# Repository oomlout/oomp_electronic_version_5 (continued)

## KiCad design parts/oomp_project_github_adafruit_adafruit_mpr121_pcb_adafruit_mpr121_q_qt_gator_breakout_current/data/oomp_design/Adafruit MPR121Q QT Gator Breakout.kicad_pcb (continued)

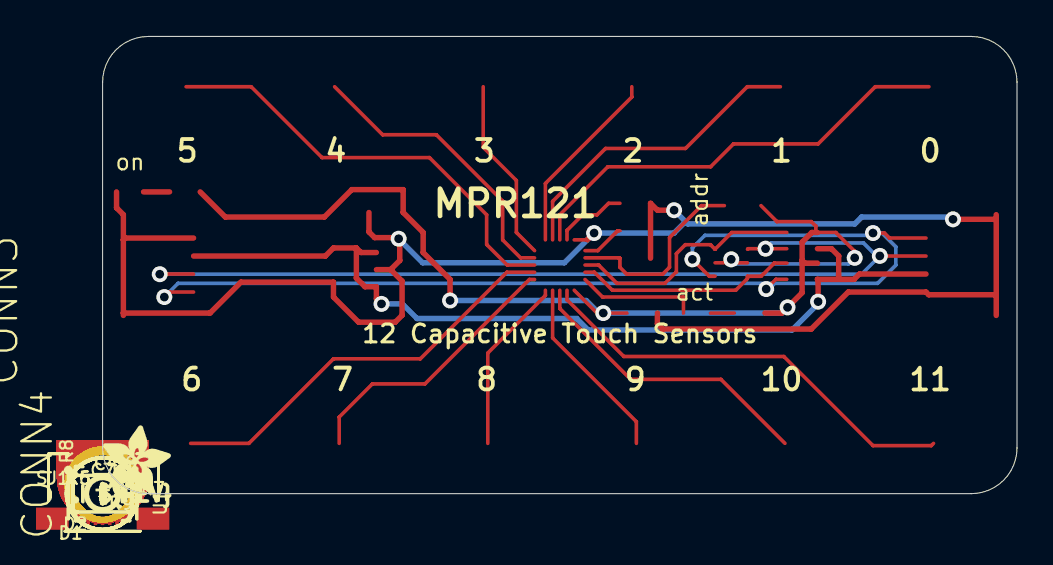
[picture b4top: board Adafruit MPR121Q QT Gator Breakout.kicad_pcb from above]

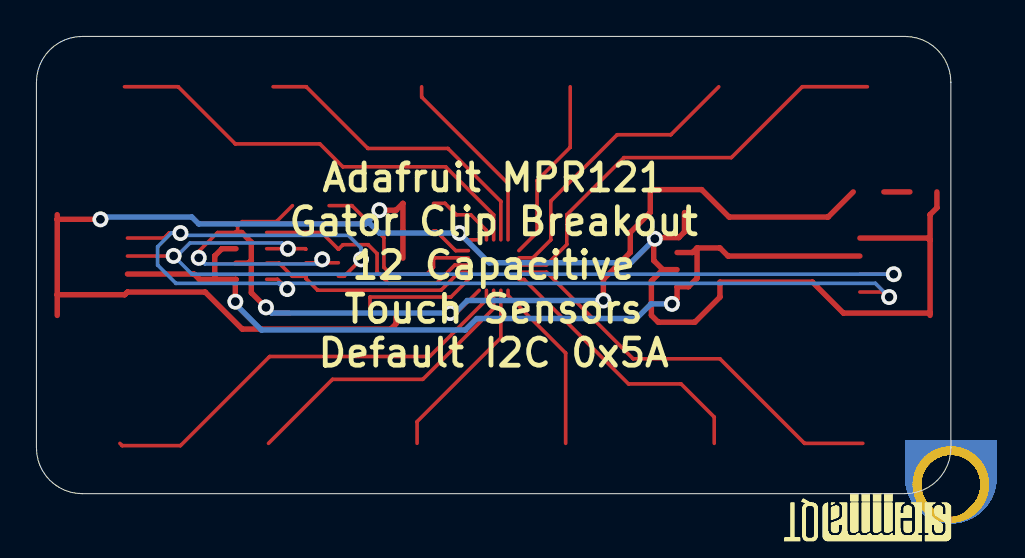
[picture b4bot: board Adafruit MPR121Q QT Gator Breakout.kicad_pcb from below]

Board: 2 copper layers, 50.8 x 25.4 mm, 39 parts (2 on the bottom side), 25 nets.

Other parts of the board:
U$10: PCBFEAT-REV-040
U$37: ADAFRUIT_3.5MM
U$39, U$40: STEMMAQT

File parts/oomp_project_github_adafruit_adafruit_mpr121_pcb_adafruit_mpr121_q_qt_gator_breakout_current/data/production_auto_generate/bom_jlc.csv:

Comment,Designator,Footprint,LCSC Part #
,U$37,Adafruit MPR121Q QT Gator Breakout-import-fps:ADAFRUIT_3.5MM,
,U$10,Adafruit MPR121Q QT Gator Breakout-import-fps:PCBFEAT-REV-040,
,"U$39,U$40",Adafruit MPR121Q QT Gator Breakout-import-fps:STEMMAQT,
0.1uF,"C4,C7",Adafruit MPR121Q QT Gator Breakout-import-fps:0603-NO,C14663
100K,R6,Adafruit MPR121Q QT Gator Breakout-import-fps:0603-NO,C25803
10K,"R7,R9",Adafruit MPR121Q QT Gator Breakout-import-fps:0603-NO,C98220
10K,R8,Adafruit MPR121Q QT Gator Breakout-import-fps:RESPACK_4X0603,C98220
10uF,"C5,C6",Adafruit MPR121Q QT Gator Breakout-import-fps:0805-NO,
75K,R5,Adafruit MPR121Q QT Gator Breakout-import-fps:0603-NO,C2907067
AP2112K-3.3,U2,Adafruit MPR121Q QT Gator Breakout-import-fps:SOT23-5,
BSS138,Q3,Adafruit MPR121Q QT Gator Breakout-import-fps:SOT363,
GREEN,D2,Adafruit MPR121Q QT Gator Breakout-import-fps:CHIPLED_0603_NOOUTLINE,
MPR121,U1,Adafruit MPR121Q QT Gator Breakout-import-fps:QFN20_3MM_NOTHERMAL,
RED,D1,Adafruit MPR121Q QT Gator Breakout-import-fps:CHIPLED_0603_NOOUTLINE,
STEMMA_I2C_QT,"CONN3,CONN4",Adafruit MPR121Q QT Gator Breakout-import-fps:JST_SH4,C160404
